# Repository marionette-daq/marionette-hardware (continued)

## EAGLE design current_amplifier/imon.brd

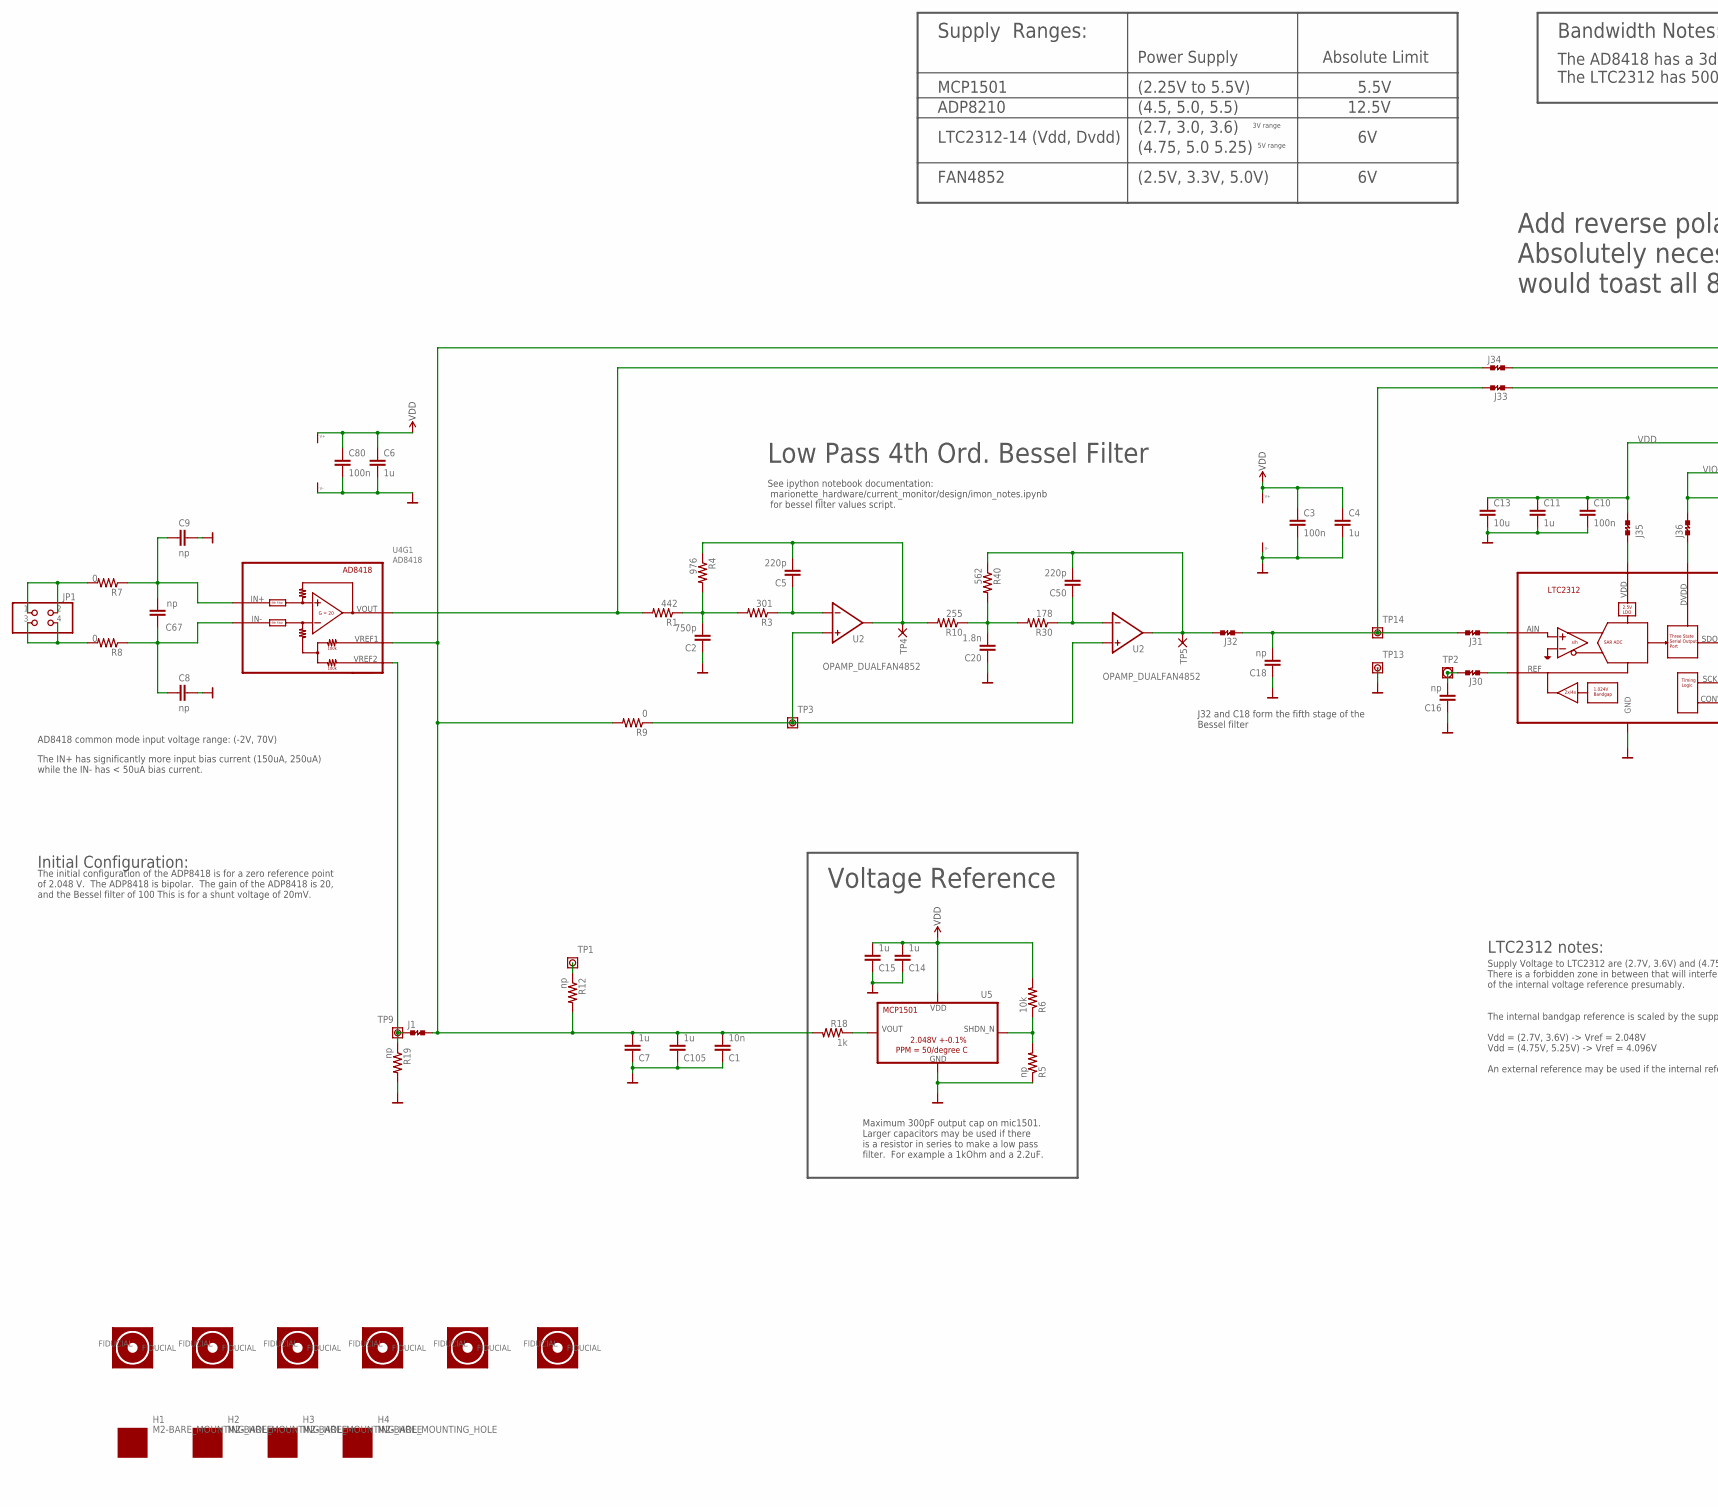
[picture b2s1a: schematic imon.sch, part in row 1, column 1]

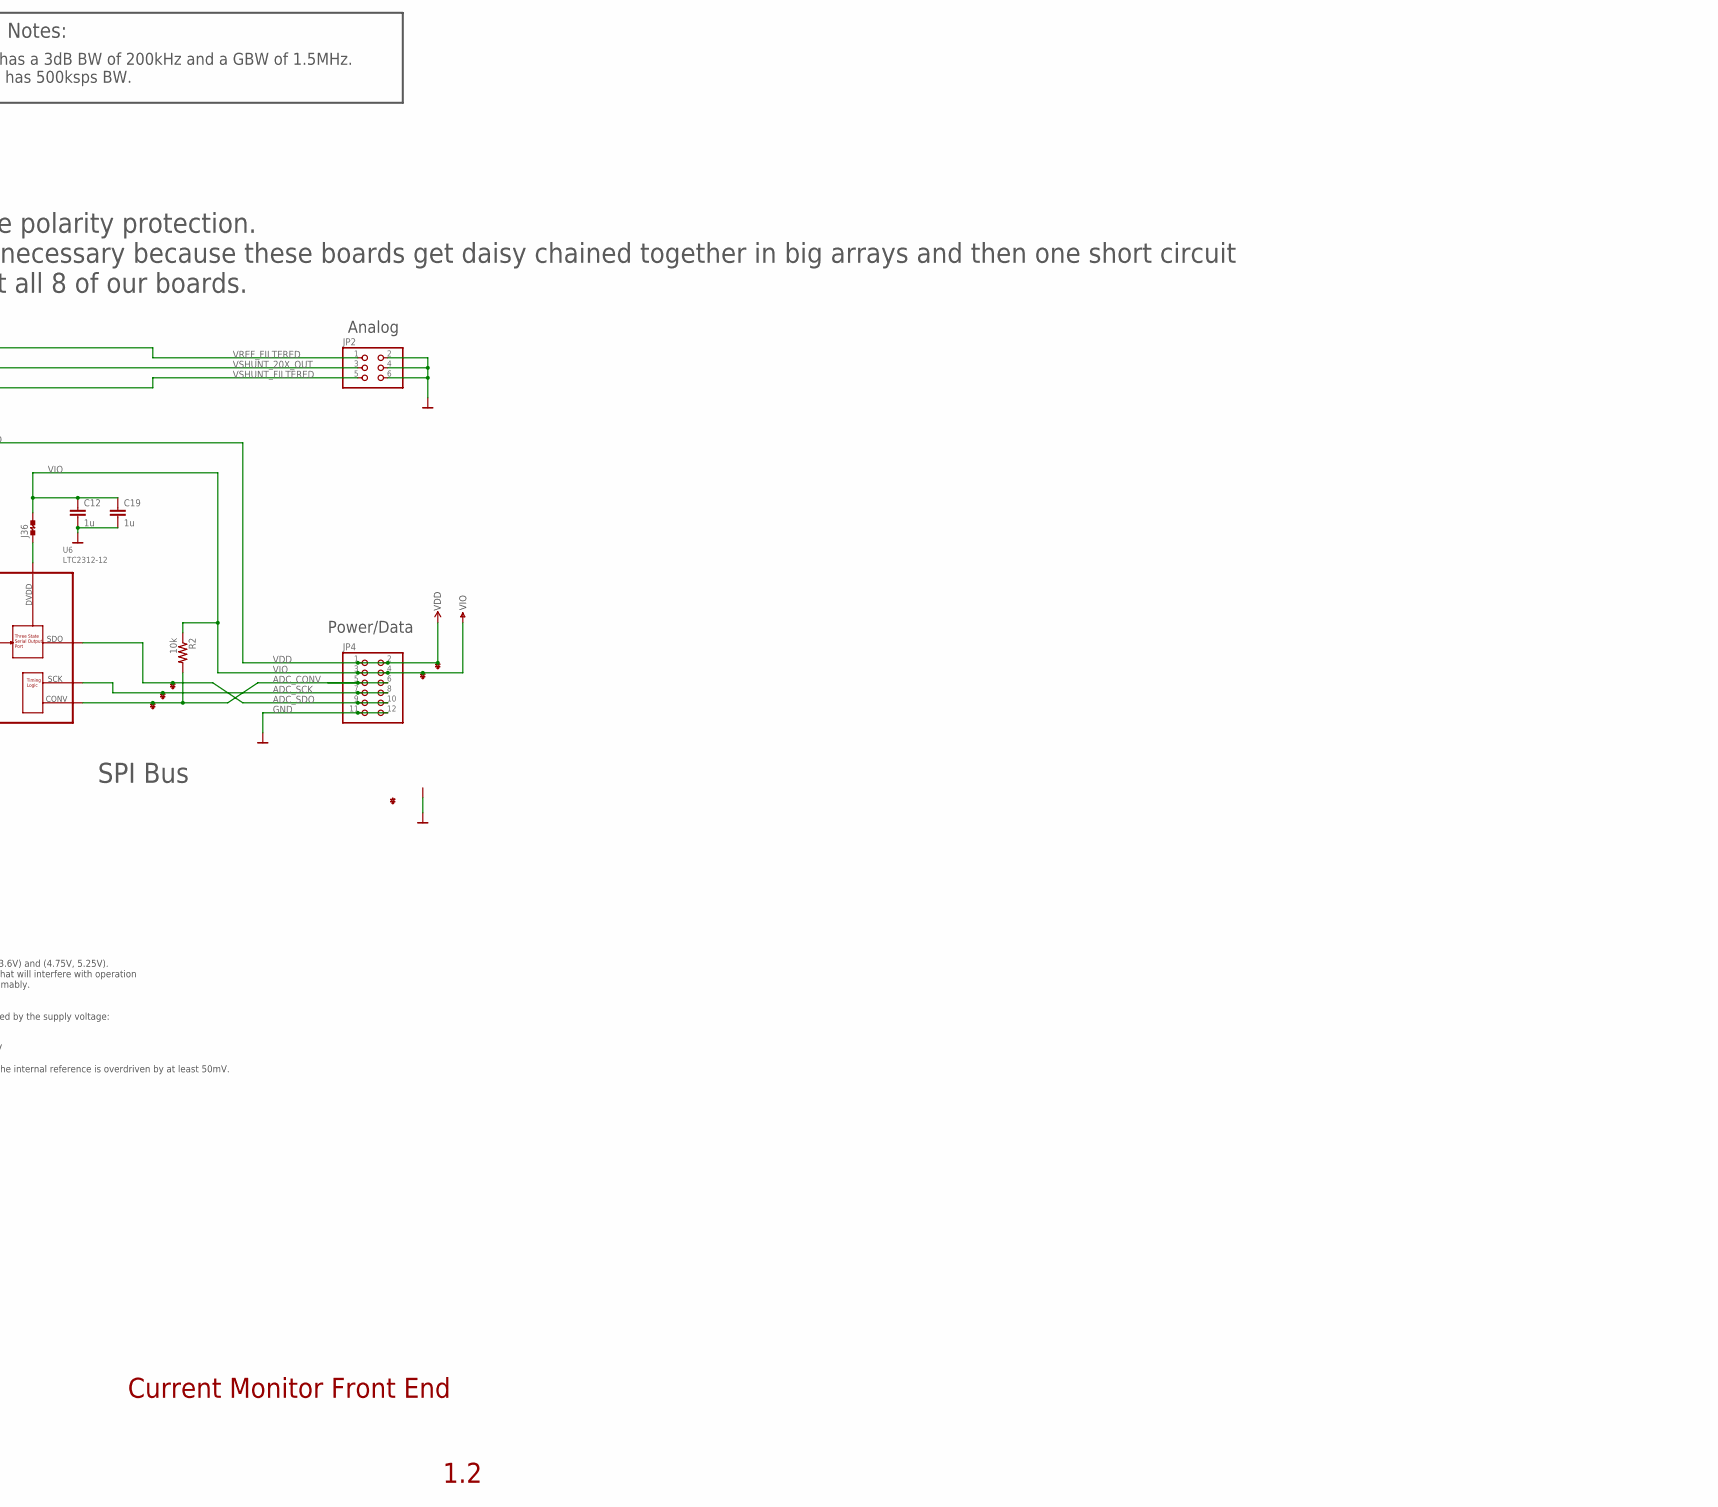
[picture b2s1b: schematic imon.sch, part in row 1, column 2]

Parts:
C1: 10n; .0402-B
C2: 750p; .0402-B
C3, C10, C80: 100n; .0402-B
C4, C6, C7, C11, C12, C14, C15, C19, C105: 1u; .0402-B
C5, C50: 220p; .0402-B
C8, C9: np; .0805-A-NOSILK
C13: 10u; .0805-B
C16, C18: np; .0402-B
C20: 1.8n; .0402-B
C67: np; 1206-0402
D1: ESD8006-ESD8006; UDFN-8-3.3X1.0_6MIL
FIDUCIAL1, FIDUCIAL2, FIDUCIAL3, FIDUCIAL4, FIDUCIAL5, FIDUCIAL6: FIDUCIAL-1.0X2.5
H1, H2, H3, H4: M2-BARE_MOUNTING_HOLE
J1, J30, J31, J32, J33, J34: JUMPER-SHORTED-CUTTABLE-E0402-0.3MM
J35, J36: JUMPER-SHORTED-CUTTABLE-E0603-0.8MM
JP1: PINHD-2X2; 2X02
JP2: PINHD-2X3; 2X03
JP4: PINHD-2X6/90; 2X06/90
R1: 442; .0402-B
R2, R6: 10k; .0402-B
R3: 301; .0402-B
R4: 976; .0402-B
R5, R12, R19: np; .0402-B
R7, R8: 0; 1206-0402
R9: 0; .0402-B
R10: 255; .0402-B
R18: 1k; .0402-B
R30: 178; .0402-B
R40: 562; .0402-B
TP1, TP9, TP14: PAD+VIA_0.25MM
TP2: PAD+VIA_0.6MM
TP3: PAD+VIA_0.3302MM
TP4, TP5: PAD+X-1.0-NO_CREAM+SILK; PAD-ROUND-1.0-NOCREAM+SILK
TP13: PAD+VIA_GND_0.25MM; PAD+GND_VIA_0.25MM
U2: OPAMP_DUALFAN4852; MSOP-8
U4: AD8418; SOIC-8_BETTER_TOE
U5: MCP1501"; SOT23-6
U6: LTC2312-12; TSOT23-8

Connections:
AD8418_REF2: J1.1, R19.1, TP9.TP, U4.3 (VREF2)
ADC_AIN: J31.1, U6.4 (AIN)
ADC_CONV: D1.4 (CATHODE), JP4.5, JP4.6, R2.2, U6.8 (CONV)
ADC_SCK: D1.2 (CATHODE), JP4.7, JP4.8, U6.7 (SCK)
ADC_SDO: D1.1 (CATHODE), JP4.9, JP4.10, U6.6 (SDO)
ADC_VREF: C16.2, J30.2, TP2.TP
ADC_VREF_CUTTABLE: J30.1, U6.2 (REF)
FILTER1-: C5.1, R3.1, U2.2 (-IN)
FILTER2-: C50.1, R30.1, U2.6 (-IN)
FILTER_1_OUT: C5.2, R4.1, R10.2, TP4.PAD, U2.1 (OUT)
FILTER_1_V1: C2.2, R1.1, R3.2, R4.2
FILTER_2_OUT: C50.2, J32.2, R40.1, TP5.PAD, U2.7 (OUT)
FILTER_2_V1: C20.2, R10.1, R30.2, R40.2
GND: C1.1, C2.1, C3.2, C4.2, C6.2, C7.1, C8.1, C9.1, C10.2, C11.2, C12.2, C13.2, C14.1, C15.1, C16.1, C18.1, C19.2, C20.1, C80.2, C105.1, D1.3 (PIN), D1.6 (PIN), D1.9 (PIN), D1.10 (PIN), JP2.2, JP2.4, JP2.6, JP4.11, JP4.12, R5.1, R19.2, TP13.TP, U2.4 (V-), U4.2 (V-), U5.2 (GND), U5.3 (GND), U5.5 (GND), U6.3 (GND)
MCP1501_SHDN_N: R5.2, R6.1, U5.4 (SHDN_N)
OPAMP_IN+: R9.1, TP3.TP, U2.3 (+IN), U2.5 (+IN)
V3.3D_CUTTABLE: J36.1, U6.5 (DVDD)
V5D_CUTTABLE: J35.1, U6.1 (VDD)
VDD: C3.1, C4.1, C6.1, C10.1, C11.1, C13.1, C14.2, C15.2, C80.1, D1.8 (CATHODE), J35.2, JP4.1, JP4.2, R6.2, U2.8 (V+), U4.6 (V+), U5.6 (VDD)
VIO: C12.1, C19.1, D1.7 (CATHODE), J36.2, JP4.3, JP4.4, R2.1
VREF_FILTERED: C1.2, C7.2, C105.2, J1.2, JP2.1, R9.2, R12.2, R18.2, U4.7 (VREF1)
VREF_OPTIONAL: R12.1, TP1.TP
VREF_OUT: R18.1, U5.1 (VOUT)
VSHUNT_20X: J34.1, R1.2, U4.5 (VOUT)
VSHUNT_20X_OUT: J34.2, JP2.3
VSHUNT_FILTERED: J33.1, JP2.5
VSHUNT_FILTERED_ADC: C18.2, J31.2, J32.1, J33.2, TP14.TP
VSHUNT_FILTERED_M: C8.2, C67.1, R8.1, U4.1 (IN-)
VSHUNT_FILTERED_P: C9.2, C67.2, R7.1, U4.8 (IN+)
VSHUNT_M: JP1.3, JP1.4, R8.2
VSHUNT_P: JP1.1, JP1.2, R7.2

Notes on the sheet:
Supply Ranges:
ADP8210
Power Supply
Absolute Limit
MCP1501
LTC2312-14 (Vdd, Dvdd)
(2.25V to 5.5V)
5.5V
12.5V
(4.5, 5.0, 5.5)
(2.7, 3.0, 3.6)
(4.75, 5.0 5.25)
3V range
5V range
SPI Bus
Low Pass 4th Ord. Bessel Filter
Maximum 300pF output cap on mic1501. Larger capacitors may be used if there is a resistor in series to make a low pass filter. For example a 1kOhm and a 2.2uF.
Current Monitor Front End
LTC2312 notes:
Supply Voltage to LTC2312 are (2.7V, 3.6V) and (4.75V, 5.25V). There is a forbidden zone in between that will interfere with operation of the internal voltage reference presumably.
The internal bandgap reference is scaled by the supply voltage: Vdd = (2.7V, 3.6V) -> Vref = 2.048V Vdd = (4.75V, 5.25V) -> Vref = 4.096V An external reference may be used if the internal reference is overdriven by at least 50mV.
See ipython notebook documentation: marionette_hardware/current_monitor/design/imon_notes.ipynb for bessel filter values script.
Initial Configuration:
The initial configuration of the ADP8418 is for a zero reference point of 2.048 V. The ADP8418 is bipolar. The gain of the ADP8418 is 20, and the Bessel filter of 100 This is for a shunt voltage of 20mV.
FAN4852
(2.5V, 3.3V, 5.0V)
J32 and C18 form the fifth stage of the Bessel filter
Power/Data
Analog
Bandwidth Notes:
The AD8418 has a 3dB BW of 200kHz and a GBW of 1.5MHz. The LTC2312 has 500ksps BW.
Voltage Reference
AD8418 common mode input voltage range: (-2V, 70V)
The IN+ has significantly more input bias current (150uA, 250uA) while the IN- has < 50uA bias current.
Add reverse polarity protection. Absolutely necessary because these boards get daisy chained together in big arrays and then one short circuit would toast all 8 of our boards.

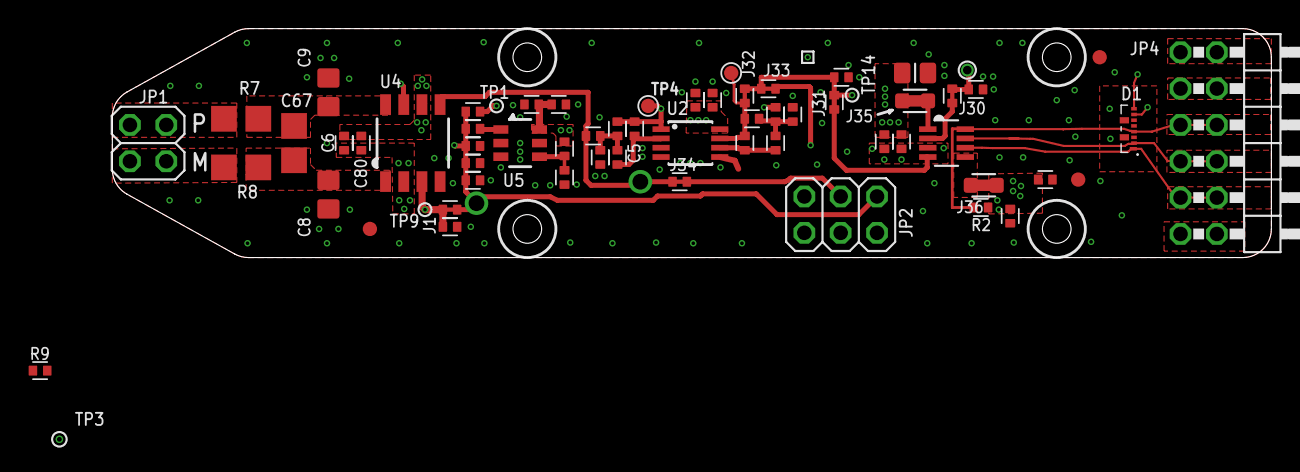
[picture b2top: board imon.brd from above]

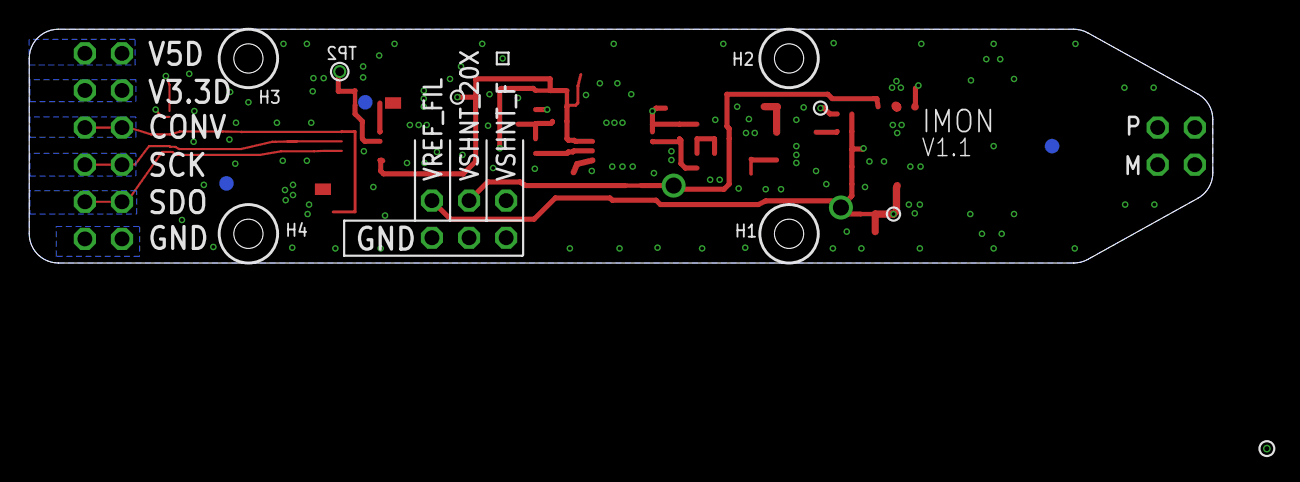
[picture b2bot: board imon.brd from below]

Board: 4 copper layers, 81.0 x 16.0 mm, 72 parts (3 on the bottom side), 31 nets.

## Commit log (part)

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2015-01-07 Starting repo...
2015-01-30 Adding power jack library
2015-01-31 Adding LDO library
2015-02-01 Adding SPS library
2015-02-03 changed part of the package outline from tdocu to tplace
2015-02-04 Pins now extend beyond symbol outline
2015-02-07 Adding resistor library
2015-02-07 Adding library description
2015-02-07 Adding Schottky diode library
2015-02-07 Updated supply symbol
2015-02-07 Simplified SPS symbol. It is less cluttered then previous version
2015-02-07 Simplified LDO symbol
2015-02-07 Edited supply symbol
2015-02-07 Added 16MHz Crystal library
2015-02-07 Added and updated crystal libraries
2015-02-07 correctly labeled the SPS library
2015-02-08 Fixed component description. ABM7 is a 16MHz crystal not 32k
2015-02-08 Modified USB3318 symbol
2015-02-08 Changed USB3318 symbol
2015-02-08 Female Pin Headers
    Added potential female pin headers for Edge Connector of Death
2015-02-10 Edited 40 female pin header. Added name and value
2015-02-12 Edited library name
2015-02-12 Renaming VDDA library
2015-02-12 Adding 32.768kHz crystal library
2015-02-12 Adding SWD debug library
2015-02-12 Added ADC bus
2015-02-12 Removed can crystal
2015-02-12 added GPIO bus
2015-02-12 added labeling to some nets
2015-02-13 Added 20pin connectors
2015-02-13 make sure git never commits stupid eagle # files.
2015-02-13 Added micro USB connectors
2015-02-14 Replaced resistors and capacitors with Marionette library components
2015-02-15 Updatede schematic and board layout
2015-02-15 Added connections to the EDGE CONNECTOR OF DEATH!!!!!!!!!!!!!
2015-02-16 Adding super capacitor library
2015-02-17 Added RGB led and resistors
2015-02-17 Created 16MHz Oscillator
2015-02-17 Added 16Mhz clock to schematic
2015-02-17 Added notes and changes from rough draft review
2015-02-19 removed 20pin female header, this wont be used
2015-02-19 Added another angled male header
2015-02-19 Added 1.8V LDO and symbol
2015-02-19 Removing Capacitor and Resistor libraries, they have been replaced by rlc_custom
2015-02-20 Added header connections for boot0 and boot1
2015-02-21 Edited Scap symbol, added 1x3 male headder, created 12bit DAC library, edited marionette schematic
2015-02-22 Added red LED
2015-02-23 edited symbol
2015-02-23 added 12x2 0.05" male header
2015-02-24 Changed footprint of parts, the pins should no longer be shorted
2015-02-24 replaced high density 0.05" header with 0.1" header.
2015-03-01 Added four output SPI controlled DAC
2015-03-01 Editied package prefix
2015-03-01 Replaced DAC chip on marionette
2015-03-02 replaced 32kHz crystal loading caps
2015-03-02 Added CAN tranceiver
2015-03-02 Added labeling
2015-03-02 Added new test pad variants
2015-03-03 Added .020, .015, .010, and .008 in test pads
2015-03-03 Added some test points
2015-03-04 Added ECOD power connector, edited header footprints and adjusted some layout
2015-03-05 Updated right angle header components. Started component placement.
2015-03-06 added 0 ohm resistor to CAN Rs
2015-03-08 Added operational amplifier and TVS array
2015-03-08 edited package prefix
2015-03-08 edited symbol and footprint
2015-03-09 TVS diodes have been added to schematic. Still need to connect SPI and DAC to TVS.
2015-03-10 placed anti-aliasing filters
2015-03-15 More ADC routing
2015-03-15 Started to route GPIO nets
2015-03-18 Increased board dimension to 5.5 x 3.0 in.
2015-03-23 Routed USB-HS PHY
2015-03-30 Most nets on left side of board are routed.
2015-03-31 Cleaned up polygons, did some minor cleanup, tented vias
2015-04-01 Cut tcream into 4 parts on the gnd pad.
2015-04-05 Routed GPIOs close to their final destinations Added TVS diodes Routed 3.3 SPS and assocaited nets
2015-04-06 Routing basically done. Todo: 1. Sort out otg_vbus net 2. Update 8 ID LED footprints 3. Update USB HS PHY footprint 4. Finish labels
2015-04-06 All nets routed!! Ready for review.
2015-04-11 Edited footprint, removed pin 20 indicator
2015-04-11 Added updated library components (USB connector)
2015-04-11 Added pushbutton for DFU bootup Added ground vias
2015-04-11 Added EEPROM footprint Added more ground vias next to various bypass caps
2015-04-12 Added pull up resistor for boot0
2015-04-12 Moved RGB LED
2015-04-13 Removed USB FS connector. Added USB3320, Routed associated nets. Moved Super CAP closer to STM
2015-04-17 Modifed pin 1 identifier
2015-04-18 Connected PB14 to ULPI refclk MCO1 is connected to a test point again cleaned up GPIO routing
2015-04-19 Replaced C42 - 0603 package with 0402 package size 0603 package size is not available
2015-04-21 fixed the 0ohm resistor to ULPI
2015-04-21 Fixed text size and ratio for tsilk
2015-04-21 Approved ERC and DRC errors that werent really errors (YAY!)
2015-04-23 Adding LM3671 lbr, 3.3V SPS
2015-04-23 Edited symbol prefix
2015-04-27 added 0805 10uF cap to 3.3sps.
2015-04-27 Adding new 1.8V LDO
2015-04-27 Added new 1.8V/3.3V LDO and associated bypass caps to schematic
2015-04-29 Added RC values for Anti-aliasing filters
2015-05-03 Adding BOM
2015-05-05 Did more on the board:
    - ZERO OHM RESISTOR ON JUMPERS
    - Fixed power and bypass cap to on-board EEPROM
    - Added 10 uF cap to uSD card.
    - Added more bypass to power supplies (0805 10u and 0603 100n to various supplies)
2015-05-05 Cleaned up silk screen.
2015-05-05 Adding marionette.cam directory and associated files
2015-05-05 Update README.md
    Adding link to BOM
2015-05-06 Added link to wiki
2015-05-07 Formatting changes, also added manufacturers part numnber field.
2015-05-07 Added component description field to spread sheet
2015-05-08 Accidently had 0603metric components instead of 0603in components. Fixed this and finished mouser partnumbers as well.
2015-05-10 Correctly connected 32.768kHz clock connection. This changed the gpio that was connected to SDIO-PWR. Minor changes to the schematic and layout. Also made some minor changes to the silk screen
2015-05-12 Adding stencil gerber
2015-05-13 Cleaned up eagle directory, moved library files into library diectory Dont forget to add this to your path in eagle :-)
2015-05-19 Changed N$* net names for ADC to something that makes sense. Also rerouted some nets that were riped up durning the namechange process.
2015-05-19 fixed label error for PD11 on sheet4 - it now is correct Shifted Net labels for gpio up by .01in - They should be easier to read
2015-06-10 Changed value of R66 from 10k to 0
2015-06-10 Corrected 3.3V SPS inductor connections. The SPS is now correct and will no longer need a mod wire. This fix is necessary as per issue #5 in the hardware repo.
2015-06-19 Edited variant labels
2015-07-02 Library contains header/cable footprints that will be used in v2
2015-07-02 corrected package size as per issue #4
2015-07-08 Standardizing connectors on the marionette, replacing ESD8008 with the ESD8006 (which has better layout characteristics)
2015-07-15 Spreadsheet that shows pin assignments of the STM32F427. This is a quick and dirty version to verify correct migration from STM407 to STM427.
2015-07-16 Marionette supply symbols all upgraded to V3.3A and V3.3D and V1.8A
2015-07-17 DAC124S085 is the correct name for the DAC chip from TI
2015-07-17 added a Questions and Todo list for the marionette
2015-07-17 Added new IDC connector 2x5
2015-07-17 Added IDC connector
2015-07-21 Changed the BUS_ID scheme to use two ADCs and fewer MUXes. Passes ERC
2015-07-21 Beginning layout of the marionette board.
2015-07-22 Redoing the power supply section to give the marionette some input protection
2015-07-28 marionette.sch ready for schematic review
2015-08-04 Incorporating changes to the schematic from the design review.
2015-08-06 design review laundry list
2015-08-06 connected USB3320_XIN to MCO1
2015-08-19 changed device name to LMV344 from LVM344
2015-08-25 placing some of the TVS diodes
2015-08-28 went to great length to equalize path lengths of SDIO and ULPI lines. Changed default package size to 0402
2015-09-03 750 air wires or so
2015-09-08 in the midst of routing the ADC buffer op amps
2015-09-08 began a marionette.lbr
2015-09-11 more signals routed
2015-09-14 routed all the GPIO lines. 380 airwires
2015-09-24 345 airwires
2015-09-30 294 airwires
2015-10-02 220 airwires
2015-11-23 < 190 airwires
2015-11-25 no airwires
2015-12-01 artwork mostly arranged. Moved fb components around in the switching power supply to minimize ground loop problems
2015-12-03 Changed routing of DM/DP to use 0603 0 ohm resistor for crossover.
2015-12-08 All of design review changes (except for library export accomplished), passes 5.5mil DRC. Zeta supply has layout facelift for smaller current loop.
2015-12-09 Major library cleanup. Ran exp-lib.ulp so that all components now point to marionette.lbr or their own particular library (i.e. DAC124S085.lbr) within the marionette_hardware/eagle/ directory. There 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
2015-12-19 Caught some problems with schematic while making BOM. The MIC5305 in fixed output voltages is not stocked at digikey (or mouser), so had to find some other fixed LDOs to substitute. Bottom line, neve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
2015-12-19 Made some small stylistic and documentation changes to some libraries
2016-02-19 Added compensation values to the marionette zeta.
2016-02-25 Added IMPORTANT note regarding the clock input, namely, Silicon versions of STM32F427 before v3 will not enter bootloader properly if given an external clock signal, i.e. a TCXO.
2016-03-18 changed some capacitor packaging on the 5V supply
2016-03-23 version notation on schematic done by GLOBAL ATTRIBUTE eagle magick
2016-03-24 marionette_v2.1 files committing for oshpark rev
2016-03-25 marionette_bom.xls added to repo
2016-04-14 Pin remapping a la The Great Gavin. Sacrificed a analog in, added more grounds, called out PWM/timer/capture pins, added more USARTs, and made a giant mess of things :(
2016-04-28 Serial connector is now done, except for some GPIO. Most of the work is done, now it's the GPIO conenctor and misc cleanup.
2016-05-19 marionette.brd
2016-05-19 Finished serial connector; pin connections are done so v2.1 should be OK to plan for wiring.
2016-05-24 Found test point missing on unused analog filter, worked with Gavin to name the pins, and in the process decided to move the CAN pins which aren't GPIO to the bottom of the serial connector.
2016-05-26 more tname cleanup, added bstop under vias in pads, schematic pretty-ification.
2016-09-08 Changed the hole size on the 20 pin and 40 pin connectors from 0.8mm to 0.914mm which will correctly receive the 0.64mm square pins. I chose 0.914mm which is 36mil from the sunstone drill rack. Going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
2016-09-14 current amplifier started
2016-09-21 imon files
2016-11-09 laying out imon.brd
2016-11-29 The current monitor board is laid out but needs some polishing
2016-12-07 Changed the gain on the Bessel filter
2016-12-14 Changed the rev number on the imon board to 1.1 . Changed the polygons on the 2x6 pin header so that the pins can go off the end of the board for low profile.
2017-01-05 added imon_notes ipython notebook
2017-03-28 some small changes
2017-04-01 DC calibration data for the current monitor boards
2018-03-29 Moved libraries into a library folder. Still probably need to be cleaned up...
2018-11-07 Committing half-way done Marionette stuff. Lots of changes on the front end, mostly power supply.
2018-11-09 marionette tweaks to the LT3414
2018-11-13 Passes ERC. Added descriptive names to the various BUSes. Routing board.
2018-11-16 marionette layout now with ltc3114 cell mostly done
2018-11-20 Passes ERC, no airwires
2018-12-12 placed the ground clips tstop/bstop
2019-01-16 adding bplace/tplace labels to the marionette board. Added Green LEDs to the board and BOM
2019-01-24 component consolidation changes made to the BOM and board.
2019-01-24 BOM updated to reflect board v2.2
2019-01-25 The latest CAM file changes the names of the layers which would result in a .build/ with v2.1 and v2.2 gerber files which is very confusing. Therefore I am committing minor git sin of making marionet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
2019-02-02 marionette_v2.2 commit
2019-02-07 README.md file added for the marionette board which is inherited from the dock.
2019-02-07 mount file for the marionette_v2.2 with the TCXO and associated filter components populated.
